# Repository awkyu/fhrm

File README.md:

# fhrm
BME 398: Fetal Heart Rate Monitor Circuit Design

This project was a small design project that was never fully realized as a proposal for an at-home Fetal Heart Rate Monitor. Signal artefacts are a major issue in current fetal heart rate sensors, leading to misdiagnoses that can lead to fetal mortality. Both Fetal Heart Rate and Fetal Movement are essential indicators for fetal health, providing information on cardiovascular and nervous system development, respectively. The device proposed here aims to limit these artefacts.

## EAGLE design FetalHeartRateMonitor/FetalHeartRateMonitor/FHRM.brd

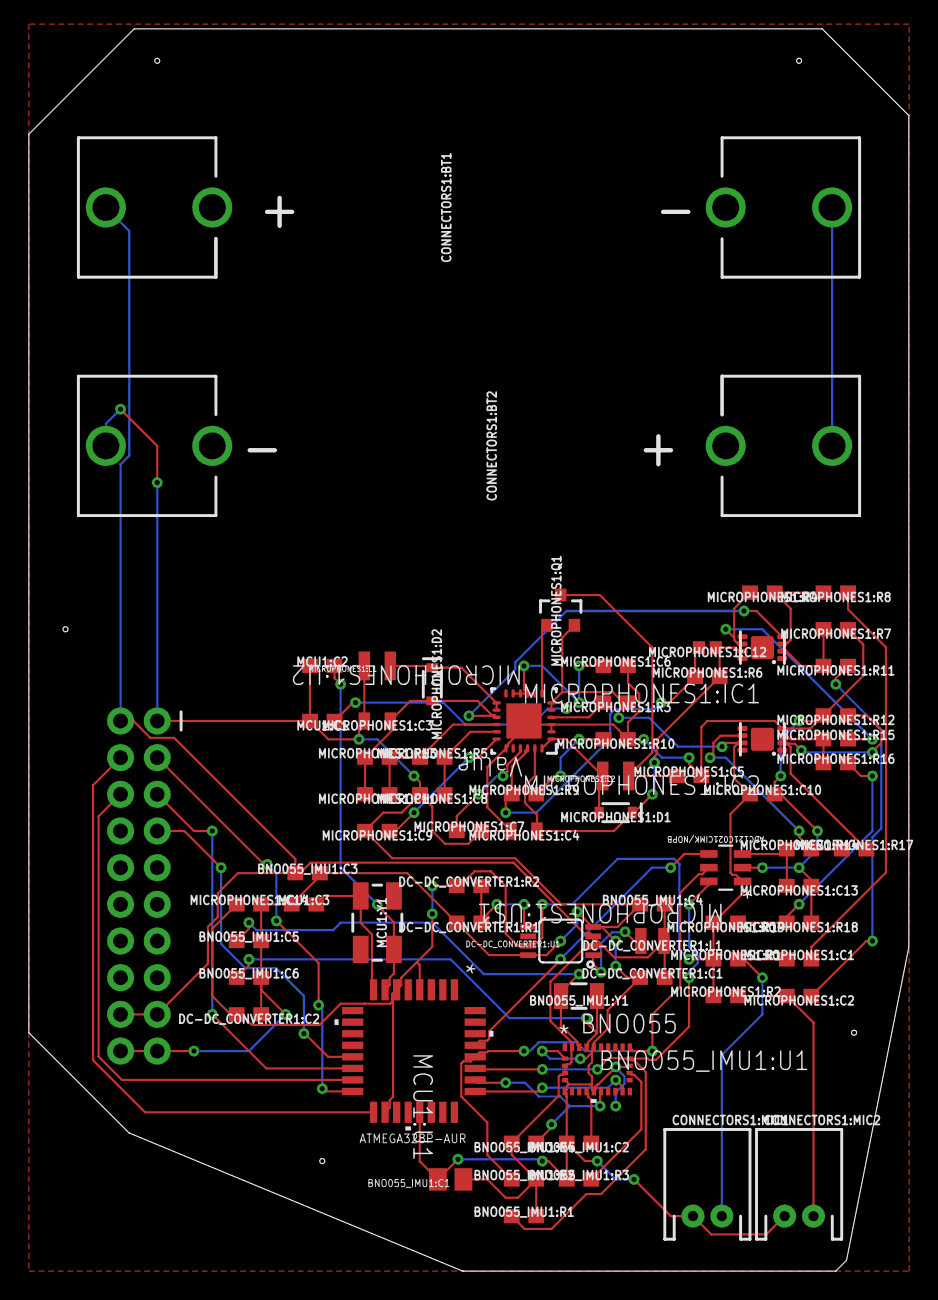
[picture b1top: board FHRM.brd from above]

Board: 2 copper layers, 60.9 x 86.0 mm, 70 parts (1 on the bottom side), 47 nets.

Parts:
BNO055_IMU1:C1: 6.8nF; CAPC2012X140N
BNO055_IMU1:C2, BNO055_IMU1:C3, BNO055_IMU1:C4: 0.1uF; 0603
BNO055_IMU1:C5, BNO055_IMU1:C6: 22pF; 0603
BNO055_IMU1:R1, BNO055_IMU1:R2, BNO055_IMU1:R3, BNO055_IMU1:R4: 10k; 0603
BNO055_IMU1:U1: BNO055; QFN_BNO055_BOS
BNO055_IMU1:Y1: 32.768kHz; CRYSTAL-SMD-3.2X1.5MM
CONNECTORS1:BT1, CONNECTORS1:BT2: BATTERY-AA
CONNECTORS1:DISPLAY: 2X10
CONNECTORS1:MIC1, CONNECTORS1:MIC2: JST-2-PTH
DC-DC_CONVERTER1:C1: 10uF; 0603
DC-DC_CONVERTER1:C2: 22uF; 0603
DC-DC_CONVERTER1:L1: 2.2μH; 0805-WIDE
DC-DC_CONVERTER1:R1: 100k; 0603
DC-DC_CONVERTER1:R2: 750K; 0603
DC-DC_CONVERTER1:U1: PAM2401; MSOP8
MCU1:C1: 10uF; 0603
MCU1:C2, MCU1:C3: 22pF; 0603
MCU1:U1: ATMEGA328P-AUR; 32A_ATM
MCU1:Y1: 16MHz; CRYSTAL-SMD-5X3.2-4PAD
MICROPHONES1:C1, MICROPHONES1:C2, MICROPHONES1:C14: 1.0uF; 0603
MICROPHONES1:C3, MICROPHONES1:C4: 22uF; 0805
MICROPHONES1:C5, MICROPHONES1:C10: 4.7uF; 0603
MICROPHONES1:C6, MICROPHONES1:C13: 0.1uF; 0603
MICROPHONES1:C7: 10nF; 0603
MICROPHONES1:C8: 0.22uF; 0603
MICROPHONES1:C9: 3.3nF; 0603
MICROPHONES1:C11: 9.0pF; 0603
MICROPHONES1:C12: 6pF; 0402
MICROPHONES1:D1, MICROPHONES1:D2: 1A/23V/620mV; SOD-323
MICROPHONES1:IC1, MICROPHONES1:IC2: ADA4627-1CP; LFCSP8
MICROPHONES1:L1, MICROPHONES1:L2: 4.7μH_SHIELDED_INDUCTOR; 1008(2520)
MICROPHONES1:Q1: 20V/4.2A/52mΩ/1.4W; SOT23-3
MICROPHONES1:R1, MICROPHONES1:R2: 1k; 0603
MICROPHONES1:R3: 100; 0603
MICROPHONES1:R4, MICROPHONES1:R7, MICROPHONES1:R8, MICROPHONES1:R11, MICROPHONES1:R18, MICROPHONES1:R19: 10k; 0603
MICROPHONES1:R5, MICROPHONES1:R9: 124k; 0603
MICROPHONES1:R6, MICROPHONES1:R13: 1M; 0603
MICROPHONES1:R10: 5.1k; 0603
MICROPHONES1:R12, MICROPHONES1:R14, MICROPHONES1:R15: 100k; 0603
MICROPHONES1:R16, MICROPHONES1:R17: 47k; 0603
MICROPHONES1:U2: Value; RGE0024B
MICROPHONES1:U$1: ADC121C021CIMK/NOPB; MK06A

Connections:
+3V3: BNO055_IMU1:C1.1, BNO055_IMU1:C3.1, BNO055_IMU1:C4.2, BNO055_IMU1:R1.2, BNO055_IMU1:R2.2, BNO055_IMU1:R4.2, BNO055_IMU1:U1.3, BNO055_IMU1:U1.4, BNO055_IMU1:U1.28, CONNECTORS1:BT1.PWR@1, CONNECTORS1:DISPLAY.2, CONNECTORS1:DISPLAY.17, CONNECTORS1:DISPLAY.18, DC-DC_CONVERTER1:C1.2, DC-DC_CONVERTER1:L1.1, DC-DC_CONVERTER1:U1.2, DC-DC_CONVERTER1:U1.3
+5V: DC-DC_CONVERTER1:C2.2, DC-DC_CONVERTER1:R2.1, DC-DC_CONVERTER1:U1.7, MCU1:C1.1, MCU1:U1.4, MCU1:U1.6, MCU1:U1.18, MICROPHONES1:C10.1, MICROPHONES1:C14.1, MICROPHONES1:IC2.7, MICROPHONES1:Q1.2, MICROPHONES1:R1.1, MICROPHONES1:R2.1, MICROPHONES1:R3.1, MICROPHONES1:R19.2, MICROPHONES1:U2.5, MICROPHONES1:U2.6, MICROPHONES1:U$1.1
BNO055_IMU1:I2C_ADDR_SEL: BNO055_IMU1:R3.2, BNO055_IMU1:U1.17
BNO055_IMU1:N$1: BNO055_IMU1:C5.1, BNO055_IMU1:U1.27, BNO055_IMU1:Y1.P$2
BNO055_IMU1:N$2: BNO055_IMU1:C2.1, BNO055_IMU1:U1.9
BNO055_IMU1:N$3: BNO055_IMU1:C6.1, BNO055_IMU1:U1.26, BNO055_IMU1:Y1.P$1
CONNECTORS1:N$1: CONNECTORS1:BT1.GND@1, CONNECTORS1:BT2.PWR@1
DC-DC_CONVERTER1:N$1: DC-DC_CONVERTER1:L1.2, DC-DC_CONVERTER1:U1.1
DC-DC_CONVERTER1:N$2: DC-DC_CONVERTER1:R1.1, DC-DC_CONVERTER1:R2.2, DC-DC_CONVERTER1:U1.5
GND: BNO055_IMU1:C1.2, BNO055_IMU1:C2.2, BNO055_IMU1:C3.2, BNO055_IMU1:C4.1, BNO055_IMU1:C5.2, BNO055_IMU1:C6.2, BNO055_IMU1:R3.1, BNO055_IMU1:U1.2, BNO055_IMU1:U1.5, BNO055_IMU1:U1.6, BNO055_IMU1:U1.10, BNO055_IMU1:U1.18, BNO055_IMU1:U1.25, CONNECTORS1:BT2.GND@1, CONNECTORS1:DISPLAY.1, CONNECTORS1:DISPLAY.19, CONNECTORS1:DISPLAY.20, CONNECTORS1:MIC1.1, CONNECTORS1:MIC2.1, DC-DC_CONVERTER1:C1.1, DC-DC_CONVERTER1:C2.1, DC-DC_CONVERTER1:R1.2, DC-DC_CONVERTER1:U1.4, DC-DC_CONVERTER1:U1.8, MCU1:C1.2, MCU1:C2.1, MCU1:C3.1, MCU1:U1.3, MCU1:U1.5, MCU1:U1.21, MICROPHONES1:C3.2, MICROPHONES1:C4.2, MICROPHONES1:C5.2, MICROPHONES1:C6.2, MICROPHONES1:C7.2, MICROPHONES1:C8.2, MICROPHONES1:C9.2, MICROPHONES1:C10.2, MICROPHONES1:C13.1, MICROPHONES1:C14.2, MICROPHONES1:IC2.4, MICROPHONES1:L1.2, MICROPHONES1:R7.1, MICROPHONES1:R10.1, MICROPHONES1:R12.2, MICROPHONES1:R18.1, MICROPHONES1:U2.2, MICROPHONES1:U2.3, MICROPHONES1:U2.19, MICROPHONES1:U2.25, MICROPHONES1:U$1.2
MCU1:N$1: MCU1:C2.2, MCU1:U1.7, MCU1:Y1.3
MCU1:N$2: MCU1:C3.2, MCU1:U1.8, MCU1:Y1.1
MICROPHONES1:N$1: MICROPHONES1:C6.1, MICROPHONES1:R3.2, MICROPHONES1:U2.4, MICROPHONES1:U2.8, MICROPHONES1:U2.9, MICROPHONES1:U2.10, MICROPHONES1:U2.11
MICROPHONES1:N$2: MICROPHONES1:C7.1, MICROPHONES1:U2.21
MICROPHONES1:N$3: MICROPHONES1:C9.1, MICROPHONES1:U2.18
MICROPHONES1:N$4: MICROPHONES1:Q1.1, MICROPHONES1:U2.7
MICROPHONES1:N$5: MICROPHONES1:C5.1, MICROPHONES1:L2.1, MICROPHONES1:Q1.3
MICROPHONES1:N$6: MICROPHONES1:D1.A, MICROPHONES1:L2.2, MICROPHONES1:U2.1, MICROPHONES1:U2.24
MICROPHONES1:N$7: MICROPHONES1:IC2.3, MICROPHONES1:R15.1, MICROPHONES1:R16.1
MICROPHONES1:N$8: MICROPHONES1:C8.1, MICROPHONES1:R5.2, MICROPHONES1:U2.17
MICROPHONES1:N$9: MICROPHONES1:C11.1, MICROPHONES1:R5.1, MICROPHONES1:R13.2, MICROPHONES1:U2.16
MICROPHONES1:N$10: MICROPHONES1:IC2.2, MICROPHONES1:R12.1, MICROPHONES1:R17.2
MICROPHONES1:N$11: MICROPHONES1:D2.C, MICROPHONES1:L1.1, MICROPHONES1:U2.13, MICROPHONES1:U2.14
MICROPHONES1:N$12: MICROPHONES1:R9.2, MICROPHONES1:R10.2
MICROPHONES1:N$13: MICROPHONES1:C12.2, MICROPHONES1:R6.1, MICROPHONES1:R9.1, MICROPHONES1:U2.22
MICROPHONES1:N$14: MICROPHONES1:C1.2, MICROPHONES1:R8.1
MICROPHONES1:N$15: MICROPHONES1:C2.1, MICROPHONES1:R11.1
MICROPHONES1:N$16: MICROPHONES1:IC1.2, MICROPHONES1:R7.2, MICROPHONES1:R11.2
MICROPHONES1:N$17: MICROPHONES1:IC1.3, MICROPHONES1:R4.1, MICROPHONES1:R8.2
MICROPHONES1:N$18: MICROPHONES1:IC1.6, MICROPHONES1:R4.2, MICROPHONES1:R15.2
MICROPHONES1:N$19: MICROPHONES1:IC2.6, MICROPHONES1:R14.2, MICROPHONES1:R17.1
MICROPHONES1:N$20: MICROPHONES1:C13.2, MICROPHONES1:R14.1, MICROPHONES1:U$1.3
MICROPHONES1:N$21: MICROPHONES1:R16.2, MICROPHONES1:R18.2, MICROPHONES1:R19.1
MICROPHONES1:VNEG: MICROPHONES1:C3.1, MICROPHONES1:C11.2, MICROPHONES1:D2.A, MICROPHONES1:IC1.4, MICROPHONES1:R13.1, MICROPHONES1:U2.15
MICROPHONES1:VPOS: MICROPHONES1:C4.1, MICROPHONES1:C12.1, MICROPHONES1:D1.C, MICROPHONES1:IC1.7, MICROPHONES1:R6.2, MICROPHONES1:U2.23
unnamed: CONNECTORS1:DISPLAY.3, MCU1:U1.16
unnamed: CONNECTORS1:DISPLAY.6, MCU1:U1.15
unnamed: CONNECTORS1:DISPLAY.4, MCU1:U1.17
unnamed: CONNECTORS1:DISPLAY.5, MCU1:U1.14
unnamed: CONNECTORS1:DISPLAY.7, MCU1:U1.13
unnamed: CONNECTORS1:MIC1.2, MICROPHONES1:C1.1, MICROPHONES1:R1.2
unnamed: CONNECTORS1:MIC2.2, MICROPHONES1:C2.2, MICROPHONES1:R2.2
unnamed: MCU1:U1.29, MICROPHONES1:U$1.4
unnamed: BNO055_IMU1:R2.1, BNO055_IMU1:U1.20, MCU1:U1.28, MICROPHONES1:U$1.5
unnamed: BNO055_IMU1:R1.1, BNO055_IMU1:U1.19, MCU1:U1.27, MICROPHONES1:U$1.6
unnamed: BNO055_IMU1:U1.14, MCU1:U1.25
unnamed: BNO055_IMU1:R4.1, BNO055_IMU1:U1.11, MCU1:U1.26

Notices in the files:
parts and their libraries:
SparkFun-Capacitors: Licensing: Creative Commons ShareAlike 4.0 International - https://creativecommons.org/licenses/by-sa/4.0
COPYRIGHT: Copyright (C) 2018 Accelerated Designs. All rights reserved
